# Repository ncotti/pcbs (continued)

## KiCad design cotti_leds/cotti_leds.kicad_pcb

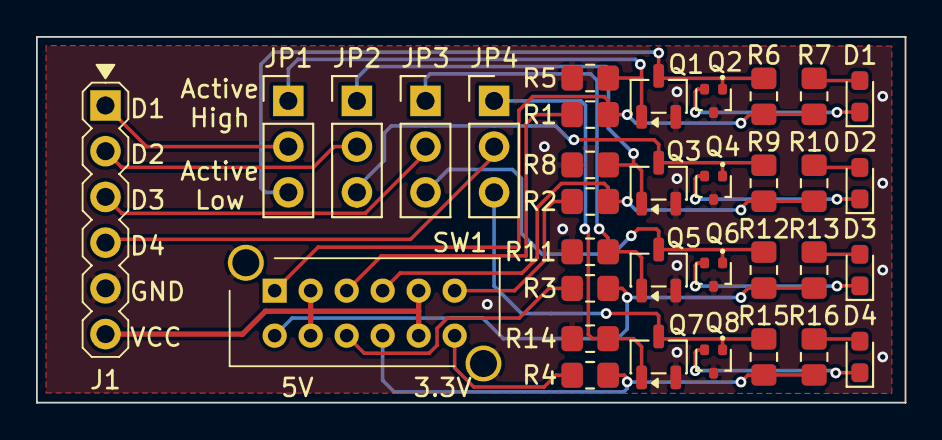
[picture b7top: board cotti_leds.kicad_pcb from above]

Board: 2 copper layers, 48.3 x 20.3 mm, 34 parts (0 on the bottom side), 30 nets.

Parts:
D1, D2, D3, D4: Red Vf=2V If=10mA; LED_0603_1608Metric_Pad1.05x0.95mm_HandSolder
J1: Pmod GPIO 1x06 pin; Pmod_1x06_pin
JP1: IO1; PinHeader_1x03_P2.54mm_Vertical
JP2: IO2; PinHeader_1x03_P2.54mm_Vertical
JP3: IO3; PinHeader_1x03_P2.54mm_Vertical
JP4: IO4; PinHeader_1x03_P2.54mm_Vertical
Q1, Q3, Q5, Q7: 2N7002K; SOT-23-3
Q2, Q4, Q6, Q8: RE1C001ZPTL; SOT-416
R1, R2, R3, R4: 200R; R_0805_2012Metric_Pad1.20x1.40mm_HandSolder
R5, R6, R8, R9, R11, R12, R14, R15: 100k; R_0805_2012Metric_Pad1.20x1.40mm_HandSolder
R7, R10, R13, R16: 22R; R_0805_2012Metric_Pad1.20x1.40mm_HandSolder
SW1: SW_4PDT

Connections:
/io1: J1.1 (IO1), JP1.2 (C)
/io1_H: JP1.1 (A), Q1.1 (G), R5.1
/io1_L: JP1.3 (B), Q1.3 (D), Q2.1 (G), R6.2
/io2: J1.2 (IO2/PWM), JP2.2 (C)
/io2_H: JP2.1 (A), Q3.1 (G), R8.1
/io2_L: JP2.3 (B), Q3.3 (D), Q4.1 (G), R9.2
/io3: J1.3 (IO3), JP3.2 (C)
/io3_H: JP3.1 (A), Q5.1 (G), R11.1
/io3_L: JP3.3 (B), Q5.3 (D), Q6.1 (G), R12.2
/io4: J1.4 (IO4), JP4.2 (C)
/io4_H: JP4.1 (A), Q7.1 (G), R14.1
/io4_L: JP4.3 (B), Q7.3 (D), Q8.1 (G), R15.2
/vcc1: R1.2, R6.1, R7.1, SW1.1 (A)
/vcc2: R2.2, R9.1, R10.1, SW1.4 (A)
/vcc3: R3.2, R12.1, R13.1, SW1.7 (A)
/vcc4: R4.2, R15.1, R16.1, SW1.10 (A)
GND: J1.5 (GND), Q1.2 (S), Q2.3 (D), Q3.2 (S), Q4.3 (D), Q5.2 (S), Q6.3 (D), Q7.2 (S), Q8.3 (D), R5.2, R8.2, R11.2, R14.2, SW1.13 (GND), SW1.14 (GND)
unnamed: D1.2 (A), R7.2
unnamed: D1.1 (K), Q2.2 (S)
unnamed: D2.2 (A), R10.2
unnamed: D2.1 (K), Q4.2 (S)
unnamed: D3.2 (A), R13.2
unnamed: D3.1 (K), Q6.2 (S)
unnamed: D4.2 (A), R16.2
unnamed: D4.1 (K), Q8.2 (S)
unnamed: R1.1, SW1.3 (C)
unnamed: R2.1, SW1.6 (C)
unnamed: R3.1, SW1.9 (C)
unnamed: R4.1, SW1.12 (C)
VCC: J1.6 (VCC), SW1.2 (B), SW1.5 (B), SW1.8 (B), SW1.11 (B)

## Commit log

2025-12-12 feat: first commit
2025-12-15 feat: pmod library
2025-12-15 feat: cotti_leds schematic
2025-12-17 feat: cotti_leds first version
2025-12-18 feat: cotti_leds v0.0
2025-12-20 feat: cotti buttons module
2025-12-21 feat: 7seg
2025-12-26 feat: level shifter
2025-12-27 feat: soldering practice first commit
2025-12-27 docs: add chatgpt answer about footprint sizes
2026-01-13 feat: nuvoton passing schematic DRC
2026-01-17 feat: cotti leds with new library format
2026-01-17 feat: cotti uttons with new libs
2026-01-17 feat: cotti leds gerber files
2026-01-17 feat: cotti buttons gerber files
2026-01-17 feat: level shifter gerbers
2026-01-18 feat: cotti 7seg gerbers
2026-01-18 fix: remove soldering practice board
2026-01-18 fix: missing descriptions in footprints and 3d model for 7seg
2026-01-18 fix: change "vcc" to "3v3" power input
2026-01-18 feat: cotti temp sensor i2c
2026-01-24 feat: gerbers for cotti probe
2026-01-24 fix: remove project libraries from cotti probe
2026-01-25 fix: length tune usb in probe
2026-01-25 fix: usb track width in probe
2026-01-31 feat: ERC passing cotti-nuvoton
2026-02-01 feat: nuvoton gerber files
